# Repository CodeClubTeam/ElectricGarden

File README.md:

# ElectricGarden

The repositories folder includes all of the files and repos that were created as part of the Electric Garden Project. Some folders include depreciated code that was no longer used in the final stage of the product.

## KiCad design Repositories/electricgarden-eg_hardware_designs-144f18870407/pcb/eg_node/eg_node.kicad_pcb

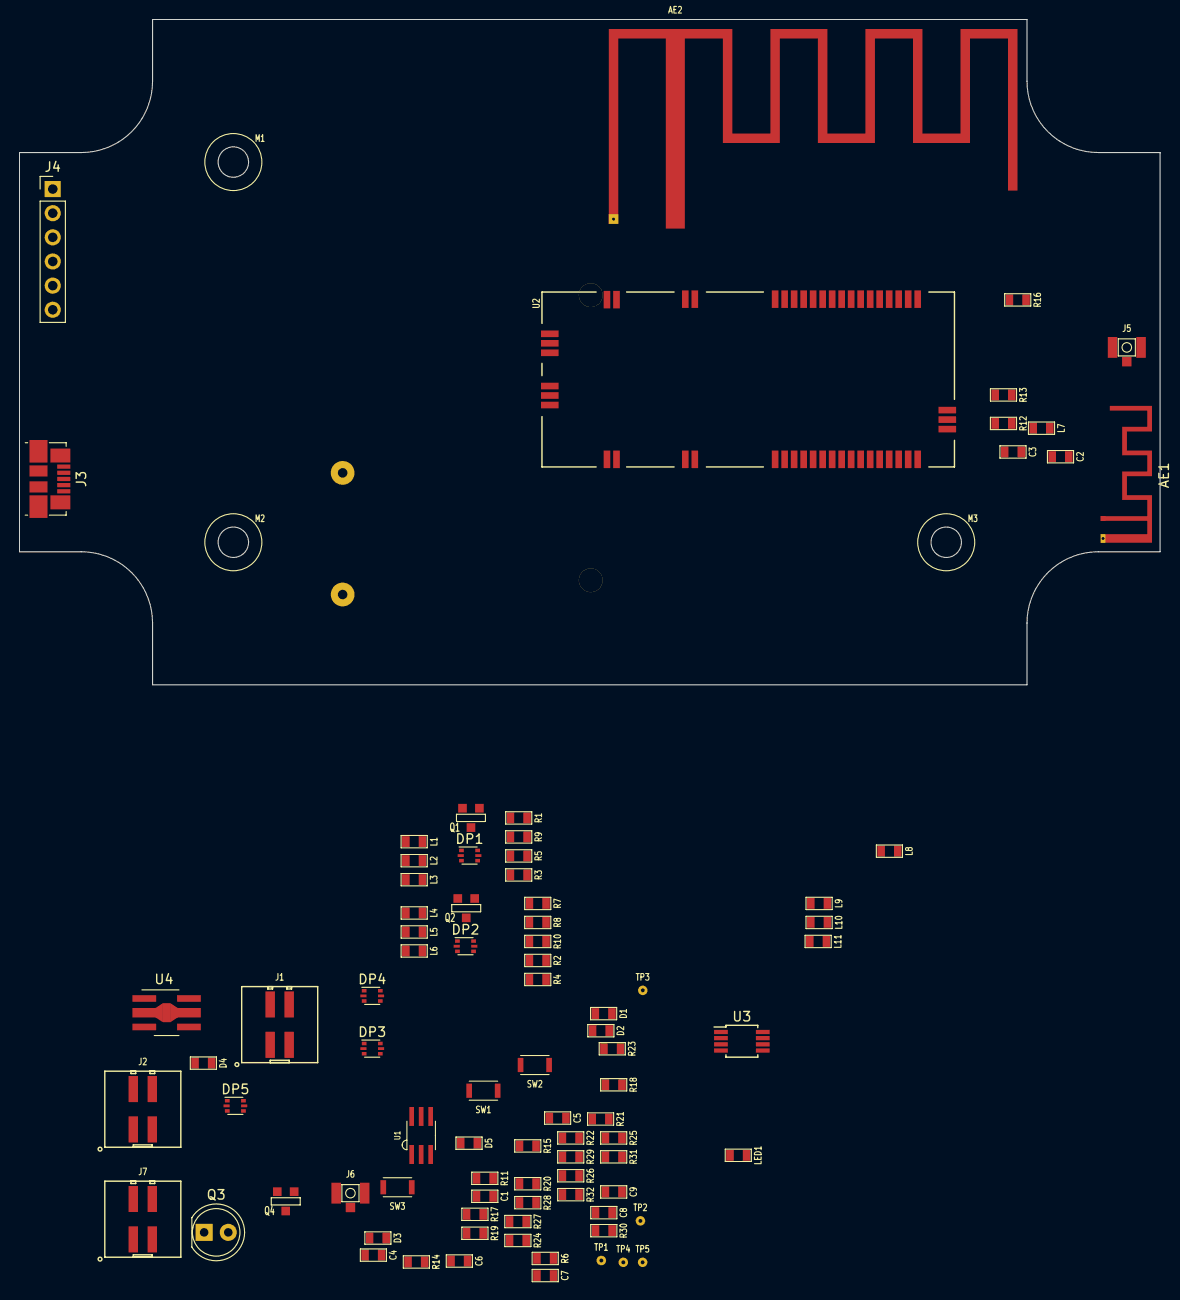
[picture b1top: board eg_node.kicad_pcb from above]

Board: 4 copper layers, 120.0 x 70.0 mm, 92 parts (1 on the bottom side), 60 nets, no tracks yet.

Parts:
AE1: Antenna_F; Texas_SWRA117D_2.4GHz_Left
AE2: Antenna_F; Texas_SWRA228C_915MHz_Right
BT1: BATTERY; MPD_BC3AAPC
C1, C4, C7: 100N; SM0603
C2, C3, C8, C9: C; SM0603
C5, C6: 10U; SM0603
D1, D5: NSR0530H; SM0603
D2, D3, D4: NSR0120; SM0603
DP1, DP2, DP4, DP5: UCLAMP3304A; SOT-666
DP3: UCLAMP0504A; SOT-666
J1, J2, J7: ConnX_F; Molex_Milligrid_02x2_2mm
J3: Micro USB; USB_Micro-B_Molex_47346-0001
J4: FTDI; Socket_Strip_Straight_1x06_Pitch2.54mm
J5, J6: Conn_Coaxial; Hirose-U.FL-R-SMT-1(40)
L1, L2, L3, L4, L5, L6, L9, L10, L11: 1k@100MHz; SM0603
L7, L8: 0R; SM0603
LED1: GREEN; SM0603
M1, M2, M3: MOUNT; hole3.2
Q1, Q2, Q4: BSS308PE H6327; SOT23GDS
Q3: LS06-S; LED_D5.0mm
R1, R2, R3, R4, R11, R31, R32: 4K7; SM0603
R5, R6, R7, R8, R29, R30: 22R; SM0603
R9, R10, R12, R13, R16, R17, R18, R19, R20, R21, R28: 0R; SM0603
R14: 1R; SM0603
R15: 68K; SM0603
R22: 330R; SM0603
R23: 1M; SM0603
R24: 500K; SM0603
R25, R26, R27: 1K; SM0603
SW1: Reset; CK_KXT_3xx
SW2: Boot; CK_KXT_3xx
SW3: Safe; CK_KXT_3xx
TP1: VBATT; Testpoint-1mm-TH
TP2: 3V3; Testpoint-1mm-TH
TP3: A-; Testpoint-1mm-TH
TP4: A+; Testpoint-1mm-TH
TP5: Aout; Testpoint-1mm-TH
U1: HDC1050; WSON6
U2: LoPy_LO4; L04_OEM
U3: LM358; MSOP-8_3x3mm_Pitch0.65mm
U4: NCP694-SOT-895; SOT-89-5_Housing_Handsoldering

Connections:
/ADC_BATT: D5.2, R23.2, R24.1, U2.26
/ADC_LIGHT: U2.27, U3.1, U3.2
/BOOT: D1.2, SW2.2, U2.9
/DEBUG_RXD: D1.1, DP4.4, J4.4, R11.2, U2.7
/DEBUG_TXD: DP4.3, J4.5, U2.8
/GND_LORA: AE2.2, C8.2, C9.2, J6.2, R21.1, U2.44, U2.46, U2.47, U2.49
/GND_WIFI: AE1.2, C2.2, C3.2, J5.2, R16.2, U2.21, U2.23
/I2CA_CTRL: Q1.G, R9.1, U2.15
/I2CA_SCL: R6.1, U2.11
/I2CA_SDA: R5.1, U2.10
/I2CB_CTRL: Q2.G, R10.1, U2.16
/I2CB_SCL: R8.1, U1.6, U2.18
/I2CB_SDA: R7.1, U1.1, U2.17
/RESET: DP4.1, J4.6, SW1.2, U2.6
/SAFE: SW3.2, U2.19
/VBATT_EN: R24.2, U2.32
/VEXTA: DP1.1, L1.2, Q1.D, R1.1, R3.1, R9.2
/VEXTB: C1.1, DP2.1, L4.2, Q2.D, R2.1, R4.1, R10.2, U1.5
/VEXTC: C7.1, DP5.1, L9.2, Q3.1, Q4.D, R28.2, R31.1, R32.1, U3.8
GND: BT1.2, C1.2, C4.2, C5.2, C6.2, C7.2, DP1.2, DP1.5, DP2.2, DP2.5, DP3.2, DP3.5, DP4.2, DP4.5, DP5.2, DP5.5, J1.1, J2.1, J3.4, J4.1, J7.1, R15.2, R16.1, R21.2, SW1.1, SW2.1, U1.2, U2.1, U2.2, U2.3, U2.4, U2.5, U2.20, U2.24, U2.25, U2.38, U2.40, U2.41, U2.42, U2.43, U3.4, U4.2
unnamed: AE1.1, C2.1, L7.2
unnamed: AE2.1, C9.1, L8.2
unnamed: C3.1, L7.1, R13.2
unnamed: C5.1, D2.1, D3.1, D4.1, R14.1, U4.3, U4.4
unnamed: C8.1, L8.1, R19.1, R20.1
unnamed: D3.2, DP3.4, J3.1
unnamed: D4.2, DP3.6, J4.3
unnamed: DP1.3, L2.2, R1.2, R5.2
unnamed: DP1.4, L3.2, R3.2, R6.2
unnamed: DP2.3, L5.2, R2.2, R7.2
unnamed: DP2.4, L6.2, R4.2, R8.2
unnamed: DP5.3, L10.2, R29.2, R32.2
unnamed: DP5.4, L11.2, R30.2, R31.2
unnamed: J1.2, L3.1
unnamed: J1.3, L2.1
unnamed: J1.4, L1.1
unnamed: J2.2, L6.1
unnamed: J2.3, L5.1
unnamed: J2.4, L4.1
unnamed: J5.1, R12.2
unnamed: J6.1, R17.1, R18.1
unnamed: J7.2, L11.1
unnamed: J7.3, L10.1
unnamed: J7.4, L9.1
unnamed: LED1.1, R22.1
unnamed: Q3.2, R15.1, U3.3
unnamed: Q4.G, R28.1, U2.35
unnamed: R12.1, R13.1, U2.22
unnamed: R17.2, R19.2, U2.48
unnamed: R18.2, R20.2, U2.45
unnamed: R22.2, U2.36
unnamed: R25.1, U3.5
unnamed: R25.2, TP4.1
unnamed: R26.1, R27.2, U3.6
unnamed: R26.2, TP3.1
unnamed: R27.1, TP5.1, U3.7
unnamed: R29.1, U2.34
unnamed: R30.1, U2.33
VCC: C4.1, C6.1, D5.1, LED1.2, Q1.S, Q2.S, Q4.S, R11.1, SW3.1, TP2.1, U2.37, U4.5
VDD2: BT1.1, D2.2, DP3.1, R14.2, R23.1, TP1.1

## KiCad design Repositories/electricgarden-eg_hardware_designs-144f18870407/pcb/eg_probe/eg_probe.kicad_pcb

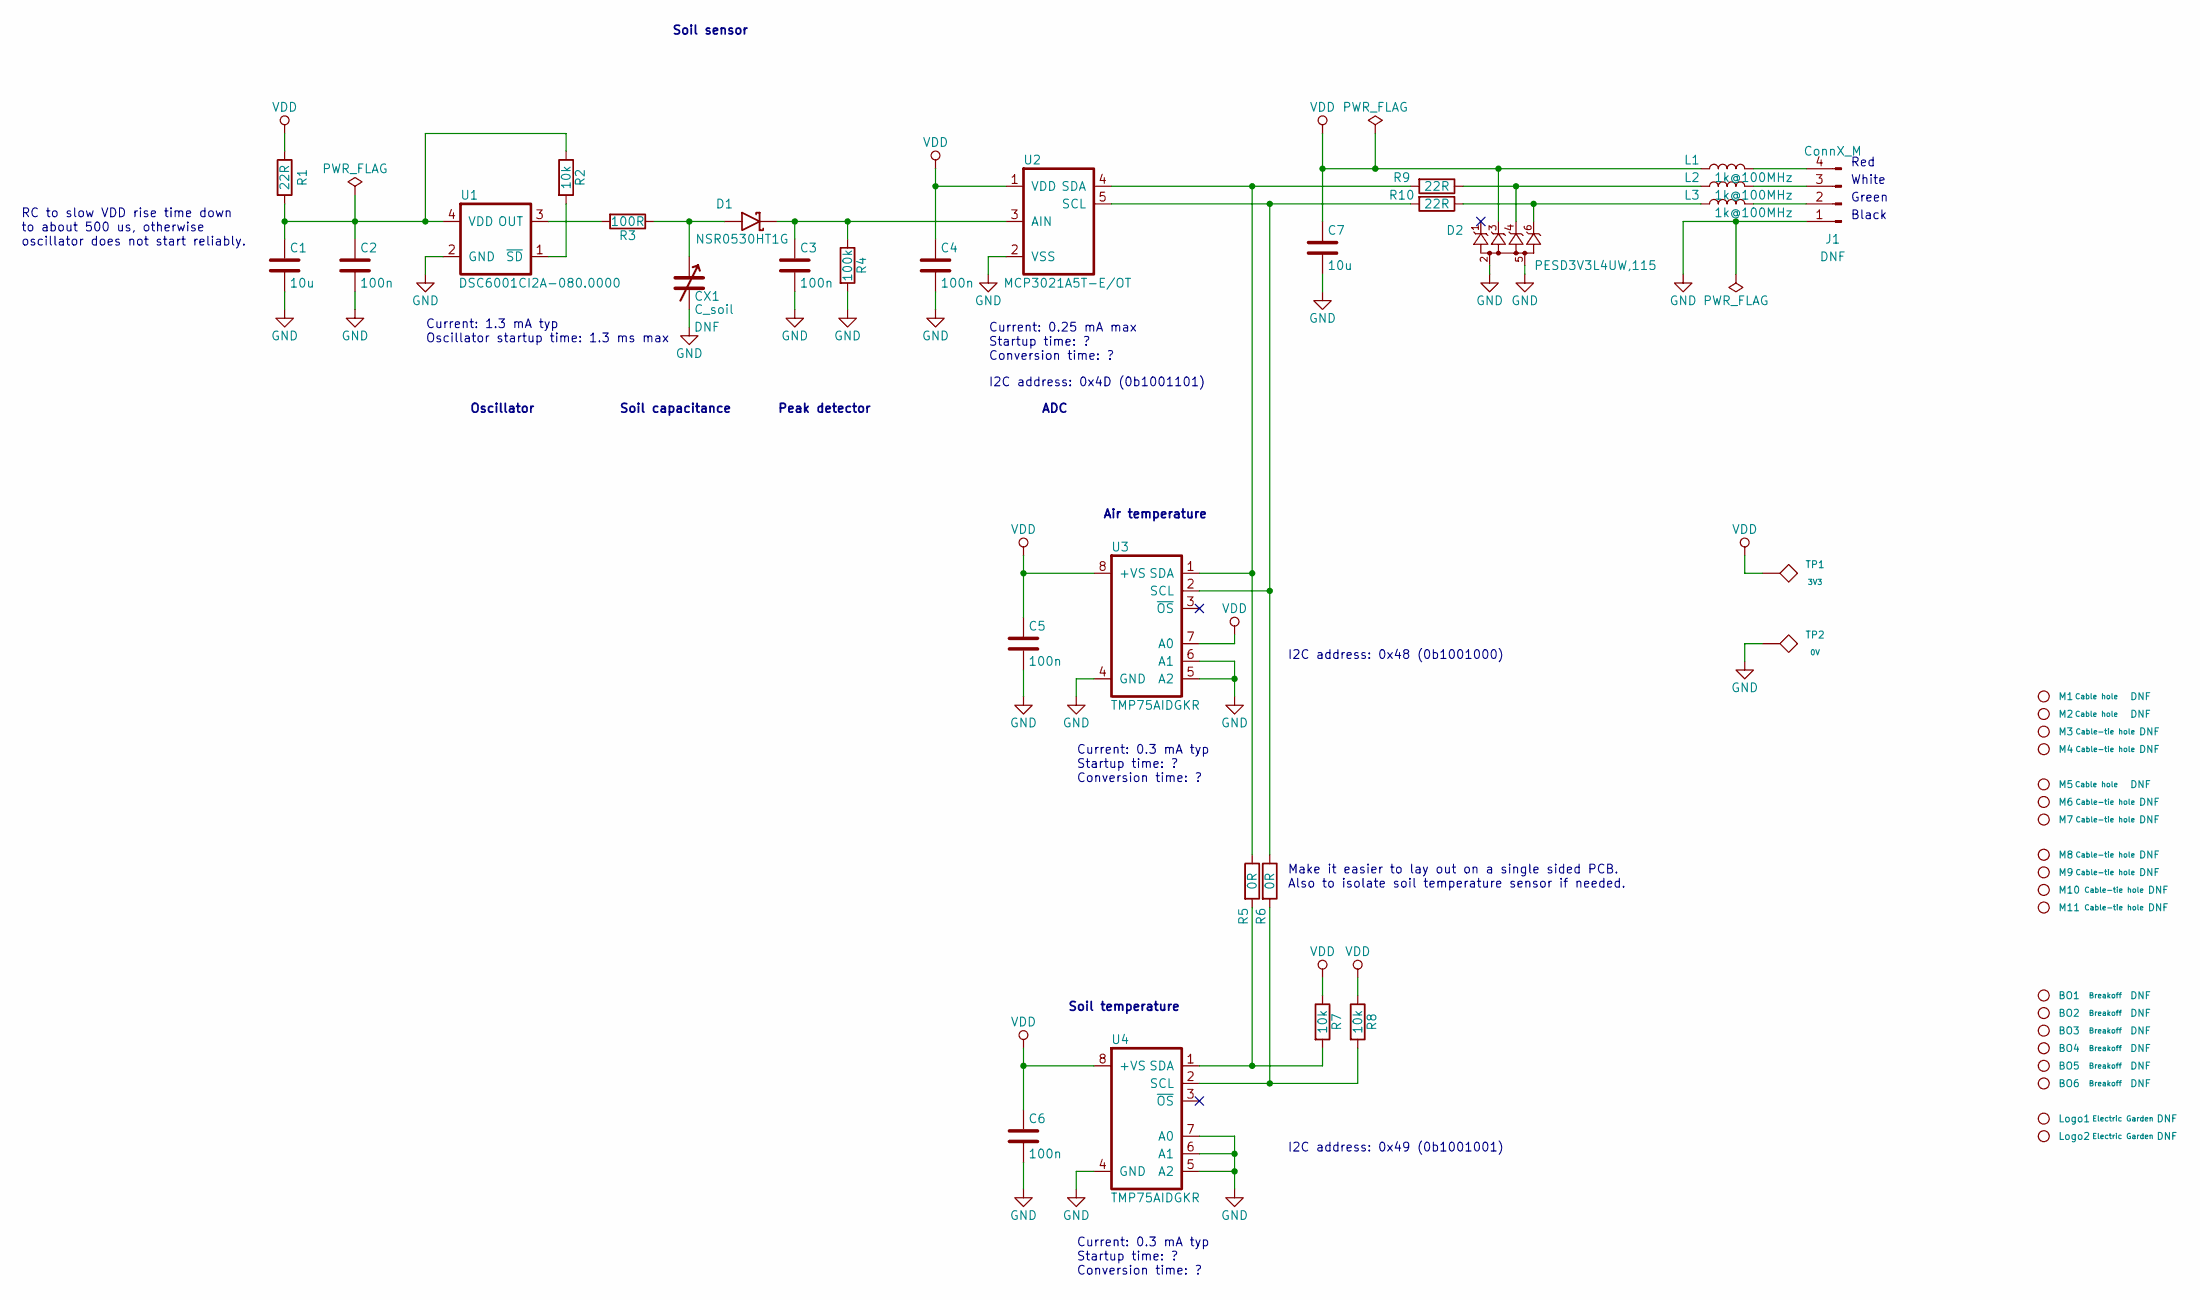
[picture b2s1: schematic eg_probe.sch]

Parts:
BO1, BO2, BO3, BO4, BO5, BO6: Breakoff; breakoff-2mm
C1, C7: 10u; SM0603
C2, C3, C4, C5, C6: 100n; SM0603
CX1: C_soil; Soil_sensor_capacitive
D1: NSR0530HT1G; D_SOD-323_HandSoldering; Part_number NSR0530HT1G
D2: PESD3V3L4UW,115; SOT-666; Part_number PESD3V3L4UW,115
J1: ConnX_M; CONN_SMD_1x4_big_pad
L1, L2, L3: 1k@100MHz; SM0603; Part_number BLM18AG102SN1D
Logo1: Electric Garden; logo-electric-garden-32x14
Logo2: Electric Garden; logo-electric-garden-25x11
M1, M2, M5: Cable hole; hole4.0
M3, M4, M6, M7, M8, M9, M10, M11: Cable-tie hole; hole3.2
R1, R9, R10: 22R; SM0603
R2, R7, R8: 10k; SM0603
R3: 100R; SM0603
R4: 100k; SM0603
R5, R6: 0R; SM0603
TP1: 3V3; TestPadSquare2.5mm
TP2: 0V; TestPadSquare2.5mm
U1: DSC6001CI2A-080.0000; DFN_4_32x25; Part_number DSC6001CI2A-080.0000
U2: MCP3021A5T-E/OT; SOT-23-5_HandSoldering; Part_number MCP3021A5T-E/OT
U3, U4: TMP75AIDGKR; S-PDSO-G8; Part_number TMP75AIDGKR

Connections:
GND: C1.2, C2.2, C3.2, C4.2, C5.2, C6.2, C7.2, CX1.2, D2.2, D2.5, J1.1, R4.2, TP2.1, U1.2 (GND), U2.2 (VSS), U3.4 (GND), U3.5 (A2), U3.6 (A1), U4.4 (GND), U4.5 (A2), U4.6 (A1), U4.7 (A0)
unnamed: C1.1, C2.1, R1.2, R2.1, U1.4 (VDD)
unnamed: C3.1, D1.2, R4.1, U2.3 (AIN)
unnamed: CX1.1, D1.1, R3.1
unnamed: D2.4, L2.1, R9.1
unnamed: D2.6, L3.1, R10.1
unnamed: J1.2, L3.2
unnamed: J1.3, L2.2
unnamed: J1.4, L1.2
unnamed: R2.2, U1.1 (~SD)
unnamed: R3.2, U1.3 (OUT)
unnamed: R5.1, R9.2, U2.4 (SDA), U3.1 (SDA)
unnamed: R5.2, R7.2, U4.1 (SDA)
unnamed: R6.2, R8.2, U4.2 (SCL)
unnamed: R6.1, R10.2, U2.5 (SCL), U3.2 (SCL)
VDD: C4.1, C5.1, C6.1, C7.1, D2.3, L1.1, R1.1, R7.1, R8.1, TP1.1, U2.1 (VDD), U3.7 (A0), U3.8 (+VS), U4.8 (+VS)

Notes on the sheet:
Peak detector
Soil capacitance
Oscillator
Soil sensor
Current: 1.3 mA typ Oscillator startup time: 1.3 ms max
ADC
Current: 0.25 mA max Startup time: ? Conversion time: ?
Air temperature
Current: 0.3 mA typ Startup time: ? Conversion time: ?
I2C address: 0x49 (0b1001001)
Red
White
Green
Black
Soil temperature
I2C address: 0x48 (0b1001000)
RC to slow VDD rise time down to about 500 us, otherwise oscillator does not start reliably.
Make it easier to lay out on a single sided PCB. Also to isolate soil temperature sensor if needed.
I2C address: 0x4D (0b1001101)

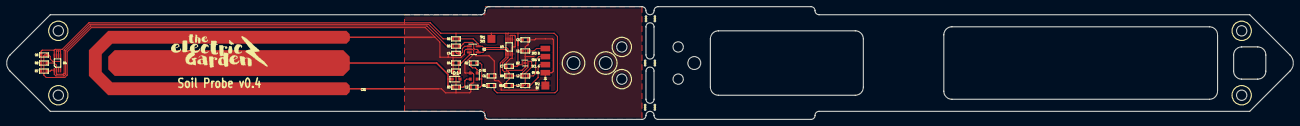
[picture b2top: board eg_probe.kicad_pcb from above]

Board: 2 copper layers, 399.6 x 35.0 mm, 49 parts (4 on the bottom side), 16 nets.

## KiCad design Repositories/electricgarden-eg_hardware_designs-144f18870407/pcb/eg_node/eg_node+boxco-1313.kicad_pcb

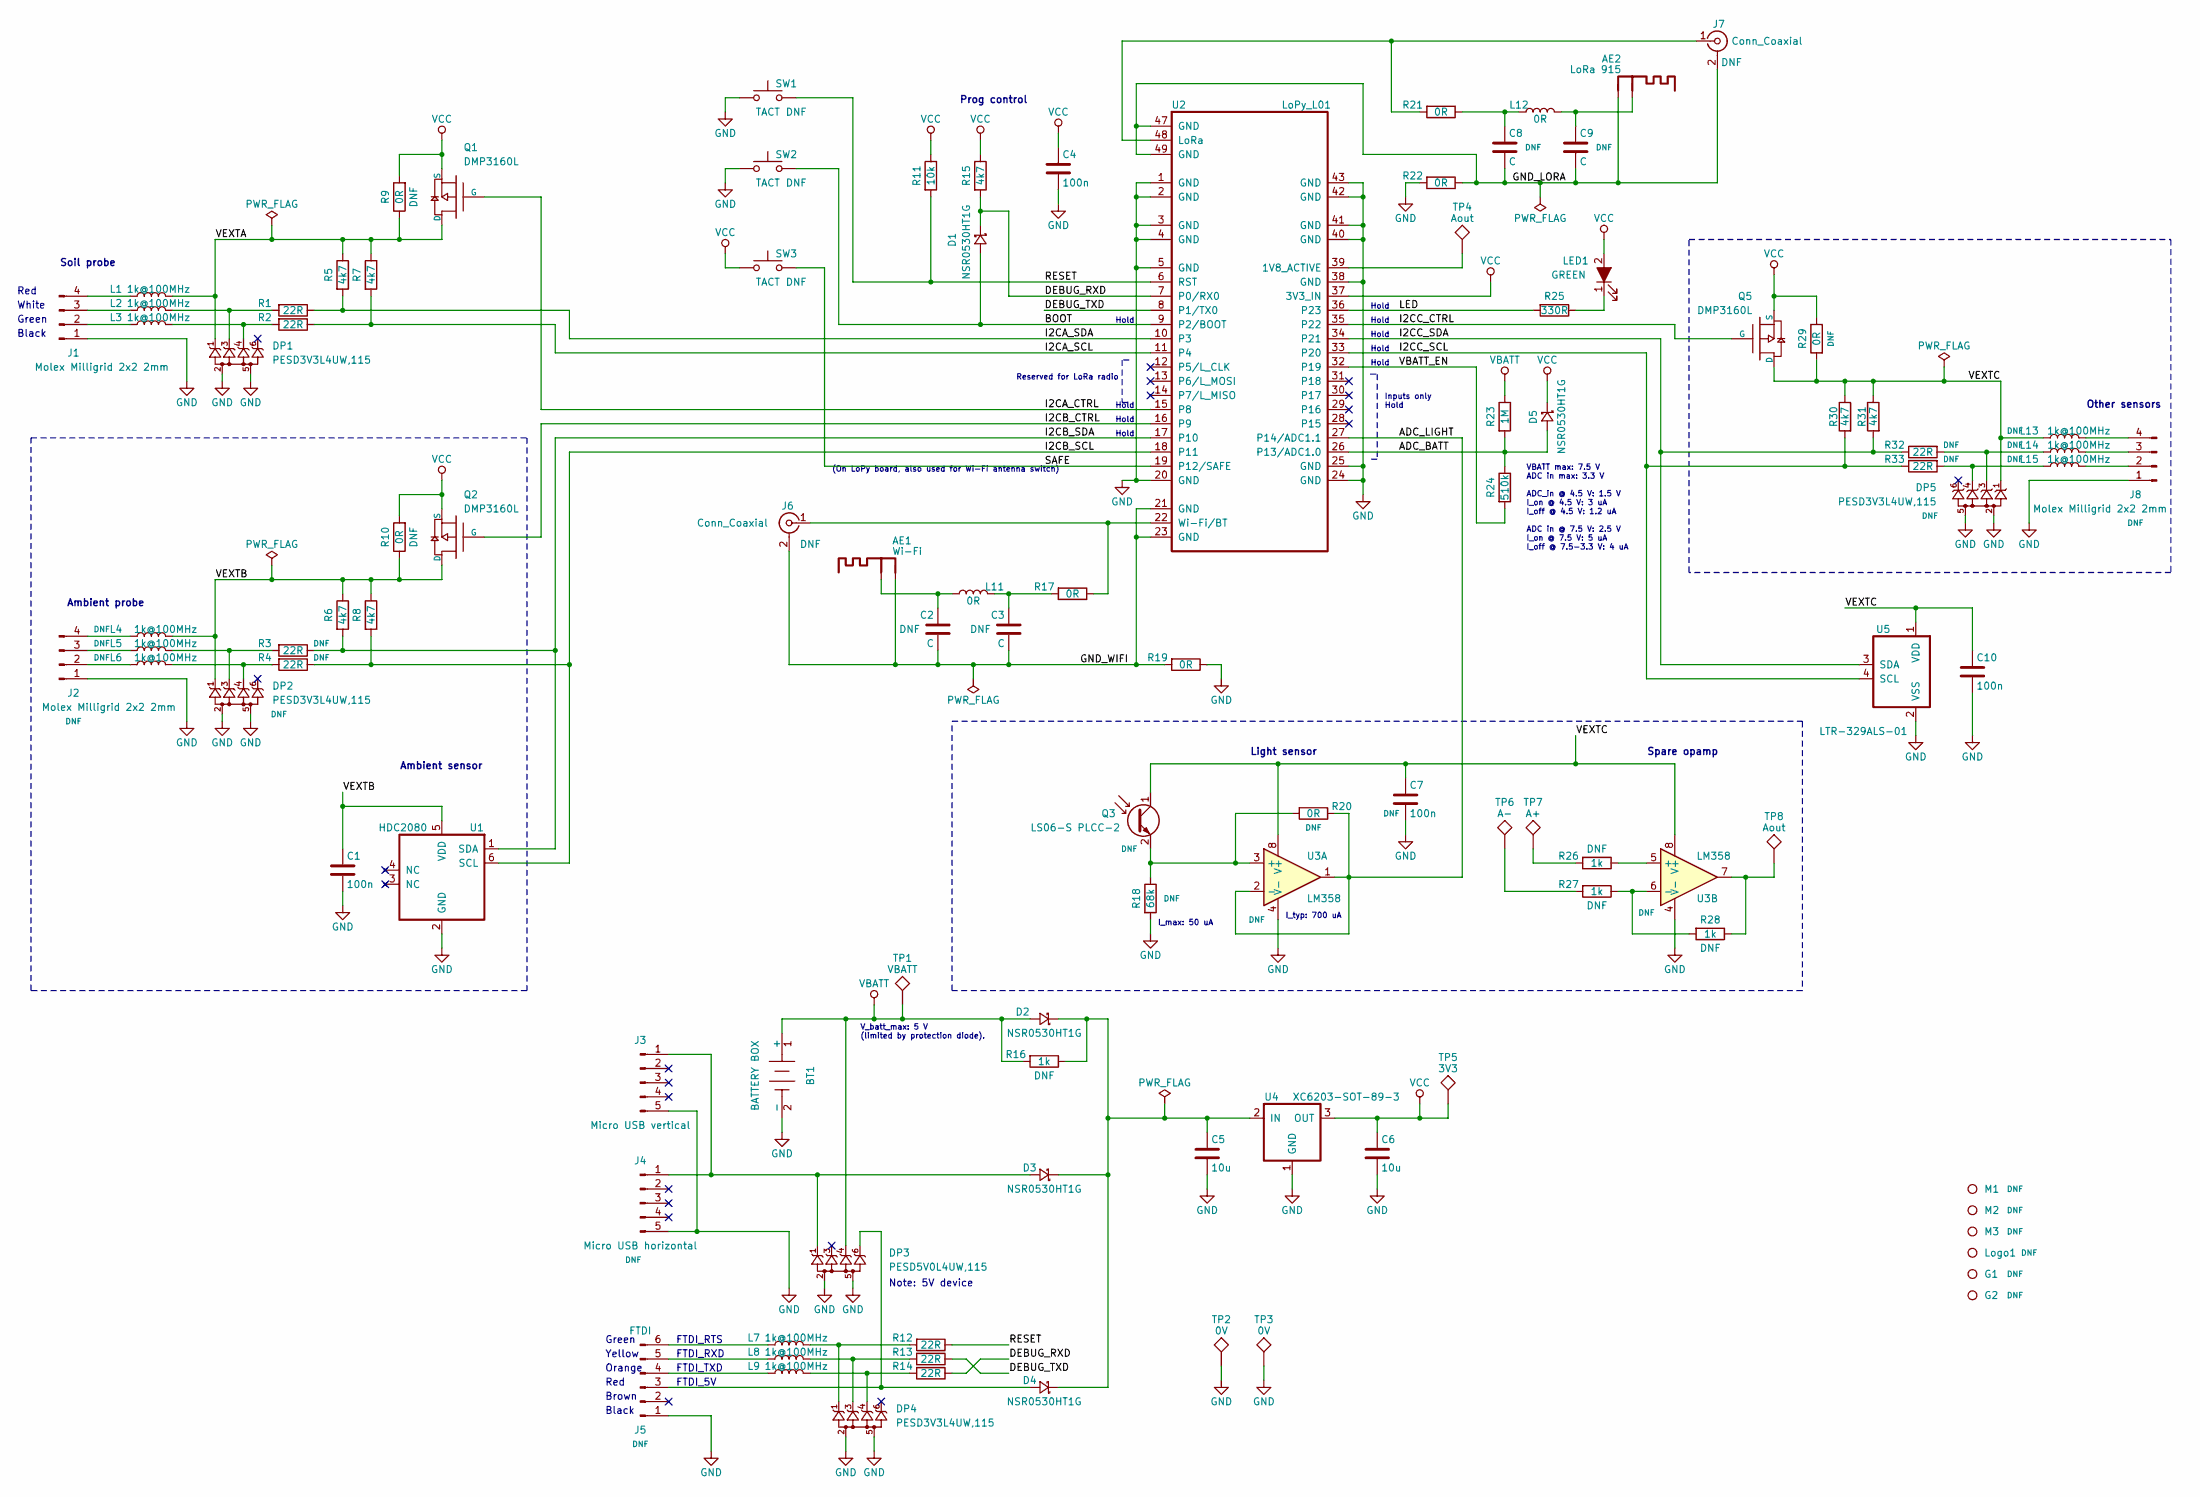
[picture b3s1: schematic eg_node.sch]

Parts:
AE1: Wi-Fi; Texas_SWRA117D_2.4GHz_Right
AE2: LoRa 915; Texas_SWRA228C_915MHz_Right
BT1: BATTERY BOX; MPD_BC3AAPC; Part_number BC3AAPC
C1, C4, C7, C10: 100n; SM0603
C2, C3, C8, C9: C; SM0603
C5, C6: 10u; SM0603
D1, D2, D3, D4, D5: NSR0530HT1G; D_SOD-323_HandSoldering; Part_number NSR0530HT1G
DP1, DP2, DP4, DP5: PESD3V3L4UW,115; SOT-666; Part_number PESD3V3L4UW,115
DP3: PESD5V0L4UW,115; SOT-666; Part_number PESD5V0L4UW,115
G1, G2: MOUNT; Boxco-gland
J1, J2, J8: Molex Milligrid 2x2 2mm; Molex_Milligrid_02x2_2mm; Part_number 87832-0406
J3: Micro USB vertical; USB_Micro-B_Vertical_Molex-105133-0001; Part_number 105133-0001
J4: Micro USB horizontal; USB_Micro-B_Molex-105017-0001; Part_number 105017-0001
J5: FTDI; Socket_Strip_Straight_1x06_Pitch2.54mm
J6, J7: Conn_Coaxial; Hirose-U.FL-R-SMT-1(40)
L1, L2, L3, L4, L5, L6, L7, L8, L9, L13, L14, L15: 1k@100MHz; SM0603; Part_number BLM18AG102SN1D
L11, L12: 0R; SM0603
LED1: GREEN; LED-0603; Part_number APT1608SGC
Logo1: Logo; logo-electric-garden-32x14
M1, M2, M3: MOUNT; hole4.5
Q1, Q2, Q5: DMP3160L; SOT23GDS; Part_number DMP3160L-7
Q3: LS06-S PLCC-2; LED_PLCC-2
R1, R2, R3, R4, R12, R13, R14, R32, R33: 22R; SM0603
R5, R6, R7, R8, R15, R30, R31: 4k7; SM0603
R9, R10, R17, R19, R20, R21, R22, R29: 0R; SM0603
R11: 10k; SM0603
R16, R26, R27, R28: 1k; SM0603
R18: 68k; SM0603
R23: 1M; SM0603
R24: 510k; SM0603
R25: 330R; SM0603
SW1, SW2, SW3: TACT; CK_KXT_3xx; Part_number KXT 331 LHS
TP1: VBATT; Testpoint-1mm-TH
TP2, TP3: 0V; scope3.5
TP4, TP8: Aout; Testpoint-1mm-TH
TP5: 3V3; Testpoint-1mm-TH
TP6: A-; Testpoint-1mm-TH
TP7: A+; Testpoint-1mm-TH
U1: HDC2080; WSON6; Part_number HDC2080DMBT
U2: LoPy_L01; LoPy_L01_OEM; Part_number L01 OEM Module
U3: LM358; MSOP-8_3x3mm_Pitch0.65mm
U4: XC6203-SOT-89-3; SOT-89-3_Handsoldering; Part_number XC6203P332PR-G
U5: LTR-329ALS-01; 4-pin-chipled; Part_number LTR-329ALS-01

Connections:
/ADC_BATT: D5.2 (A), R23.2, R24.1, U2.26 (P13/ADC1.0)
/ADC_LIGHT: R20.1, U2.27 (P14/ADC1.1), U3.1, U3.2 (-)
/BOOT: D1.2 (A), SW2.2, U2.9 (P2/BOOT)
/DEBUG_RXD: D1.1 (K), R14.1, R15.2, U2.7 (P0/RX0)
/DEBUG_TXD: R13.1, U2.8 (P1/TX0)
/GND_LORA: AE2.2 (GND), C8.2, C9.2, J7.2 (Ext), R22.1, U2.47 (GND), U2.49 (GND)
/GND_WIFI: AE1.2 (GND), C2.2, C3.2, J6.2 (Ext), R19.2, U2.21 (GND), U2.23 (GND)
/I2CA_CTRL: Q1.G, U2.15 (P8)
/I2CA_SCL: R2.1, R7.2, U2.11 (P4)
/I2CA_SDA: R1.1, R5.2, U2.10 (P3)
/I2CB_CTRL: Q2.G, U2.16 (P9)
/I2CB_SCL: R4.1, R8.2, U1.6 (SCL), U2.18 (P11)
/I2CB_SDA: R3.1, R6.2, U1.1 (SDA), U2.17 (P10)
/I2CC_CTRL: Q5.G, U2.35 (P22)
/I2CC_SCL: R30.2, R33.1, U2.33 (P20), U5.4 (SCL)
/I2CC_SDA: R31.2, R32.1, U2.34 (P21), U5.3 (SDA)
/LED: R25.2, U2.36 (P23)
/RESET: R11.2, R12.1, SW1.2, U2.6 (RST)
/SAFE: SW3.2, U2.19 (P12/SAFE)
/VBATT_EN: R24.2, U2.32 (P19)
/VEXTA: DP1.1, L1.2, Q1.D, R5.1, R7.1, R9.1
/VEXTB: C1.1, DP2.1, L4.2, Q2.D, R6.1, R8.1, R10.1, U1.5 (VDD)
/VEXTC: C7.1, C10.1, DP5.1, L13.2, Q3.1 (C), Q5.D, R29.2, R30.1, R31.1, U3.8 (V+), U5.1 (VDD)
GND: BT1.2 (-), C1.2, C4.2, C5.2, C6.2, C7.2, C10.2, DP1.2, DP1.5, DP2.2, DP2.5, DP3.2, DP3.5, DP4.2, DP4.5, DP5.2, DP5.5, J1.1, J2.1, J3.5, J4.5, J5.1, J8.1, R18.2, R19.1, R22.2, SW1.1, SW2.1, TP2.1, TP3.1, U1.2 (GND), U2.1 (GND), U2.2 (GND), U2.3 (GND), U2.4 (GND), U2.5 (GND), U2.20 (GND), U2.24 (GND), U2.25 (GND), U2.38 (GND), U2.40 (GND), U2.41 (GND), U2.42 (GND), U2.43 (GND), U3.4 (V-), U4.1 (GND), U5.2 (VSS)
unnamed: AE1.1 (A), C2.1, L11.2
unnamed: AE2.1 (A), C9.1, L12.2
unnamed: C3.1, L11.1, R17.2
unnamed: C5.1, D2.1 (K), D3.1 (K), D4.1 (K), R16.1, U4.2 (IN)
unnamed: C8.1, L12.1, R21.1
unnamed: D3.2 (A), DP3.1, J3.1, J4.1
unnamed: D4.2 (A), DP3.6, J5.3
unnamed: DP1.3, L2.2, R1.2
unnamed: DP1.4, L3.2, R2.2
unnamed: DP2.3, L5.2, R3.2
unnamed: DP2.4, L6.2, R4.2
unnamed: DP4.1, L7.2, R12.2
unnamed: DP4.3, L8.2, R13.2
unnamed: DP4.4, L9.2, R14.2
unnamed: DP5.3, L14.2, R32.2
unnamed: DP5.4, L15.2, R33.2
unnamed: J1.2, L3.1
unnamed: J1.3, L2.1
unnamed: J1.4, L1.1
unnamed: J2.2, L6.1
unnamed: J2.3, L5.1
unnamed: J2.4, L4.1
unnamed: J5.4, L9.1
unnamed: J5.5, L8.1
unnamed: J5.6, L7.1
unnamed: J6.1 (In), R17.1, U2.22 (Wi-Fi/BT)
unnamed: J7.1 (In), R21.2, U2.48 (LoRa)
unnamed: J8.2, L15.1
unnamed: J8.3, L14.1
unnamed: J8.4, L13.1
unnamed: LED1.1 (K), R25.1
unnamed: Q3.2 (E), R18.1, R20.2, U3.3 (+)
unnamed: R26.1, U3.5 (+)
unnamed: R26.2, TP7.1
unnamed: R27.1, R28.2, U3.6 (-)
unnamed: R27.2, TP6.1
unnamed: R28.1, TP8.1, U3.7
unnamed: TP4.1, U2.39 (1V8_ACTIVE)
VCC: C4.1, C6.1, D5.1 (K), LED1.2 (A), Q1.S, Q2.S, Q5.S, R9.2, R10.2, R11.1, R15.1, R29.1, SW3.1, TP5.1, U2.37 (3V3_IN), U4.3 (OUT)
VDD2: BT1.1 (+), D2.2 (A), DP3.4, R16.2, R23.1, TP1.1

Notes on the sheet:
Light sensor
Spare opamp
Black
Brown
Red
Orange
Yellow
Green
Ambient sensor
Reserved for LoRa radio
Inputs only Hold
Prog control
FTDI_RTS
FTDI_RXD
FTDI_TXD
FTDI_5V
VBATT max: 7.5 V ADC in max: 3.3 V
Soil probe
Ambient probe
Other sensors
I_max: 50 uA
I_typ: 700 uA
ADC_in @ 4.5 V: 1.5 V I_on @ 4.5 V: 3 uA I_off @ 4.5 V: 1.2 uA
ADC in @ 7.5 V: 2.5 V I_on @ 7.5 V: 5 uA I_off @ 7.5-3.3 V: 4 uA
Note: 5V device
V_batt_max: 5 V (limited by protection diode).
White
Hold
(On LoPy board, also used for Wi-Fi antenna switch)

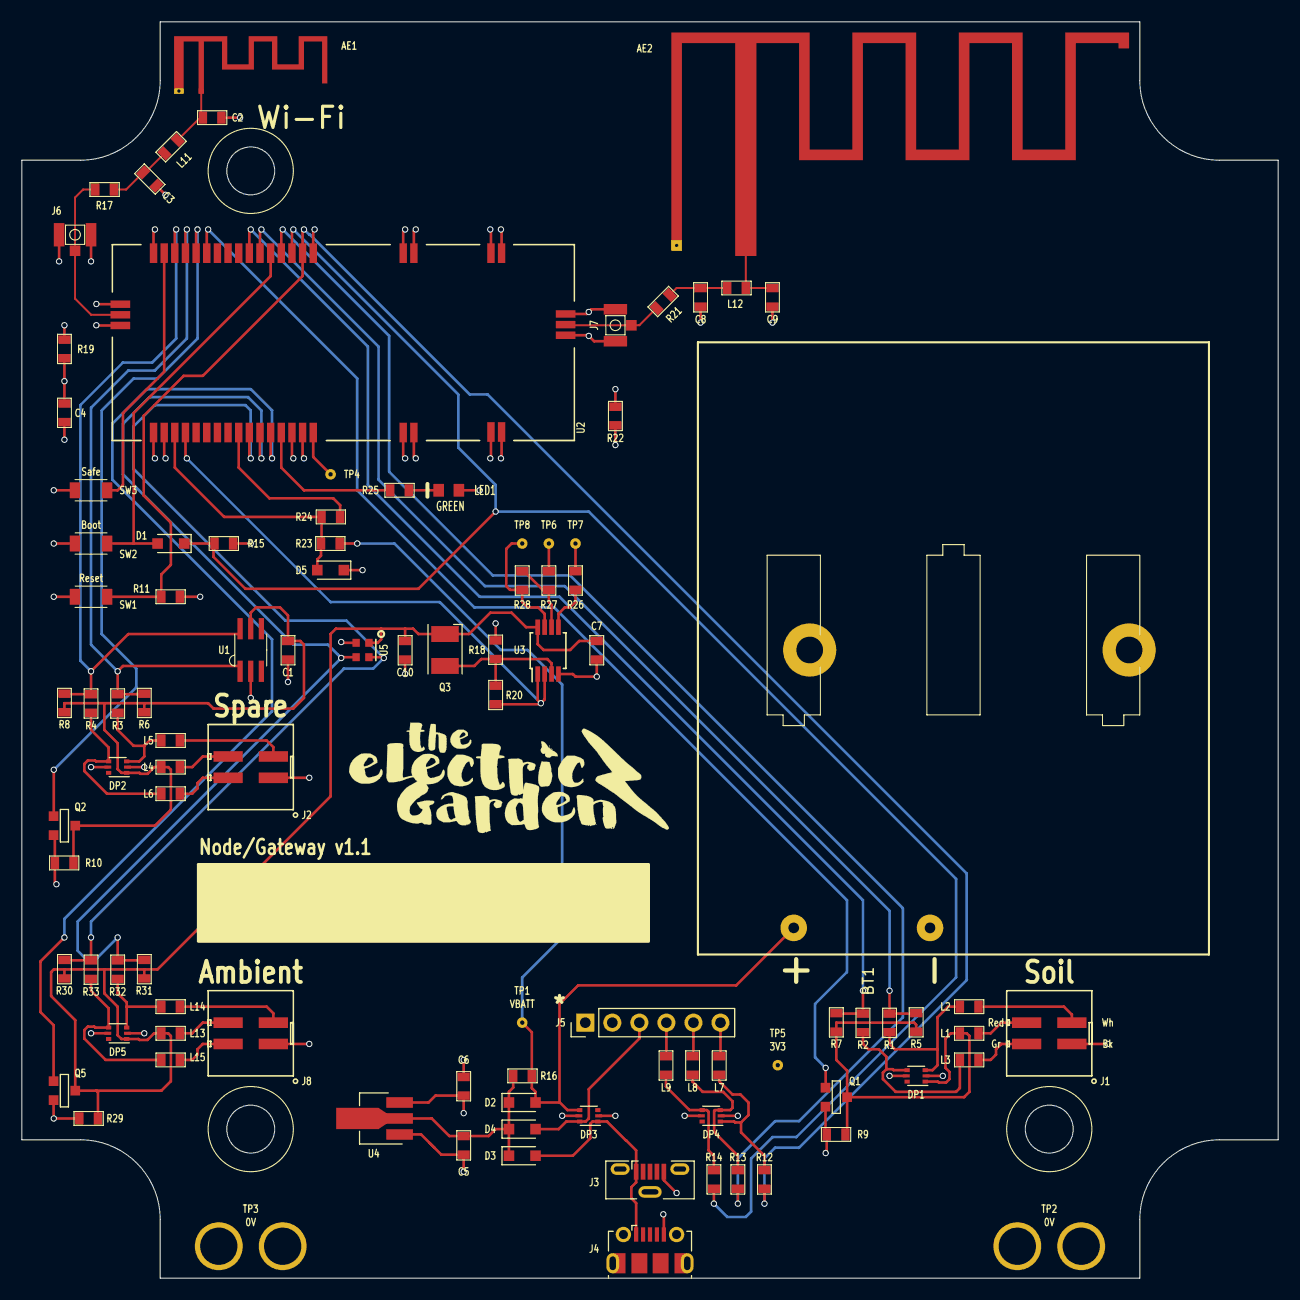
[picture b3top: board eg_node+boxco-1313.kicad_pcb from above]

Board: 4 copper layers, 118.0 x 118.0 mm, 105 parts (0 on the bottom side), 64 nets.

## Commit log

2023-07-12 README
2023-07-12 Added bitbucket repositories to folder
